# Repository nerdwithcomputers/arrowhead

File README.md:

ARROWHEAD
=========

This is my crack at a cyberdeck that not only I would want to use on the daily as I'm heading to college, but other people would want to use. I decided to go with a traditional clamshell design, which is boring, but only because that might be the only traditional thing on the device (and making sliding mechanisms that last is hard).

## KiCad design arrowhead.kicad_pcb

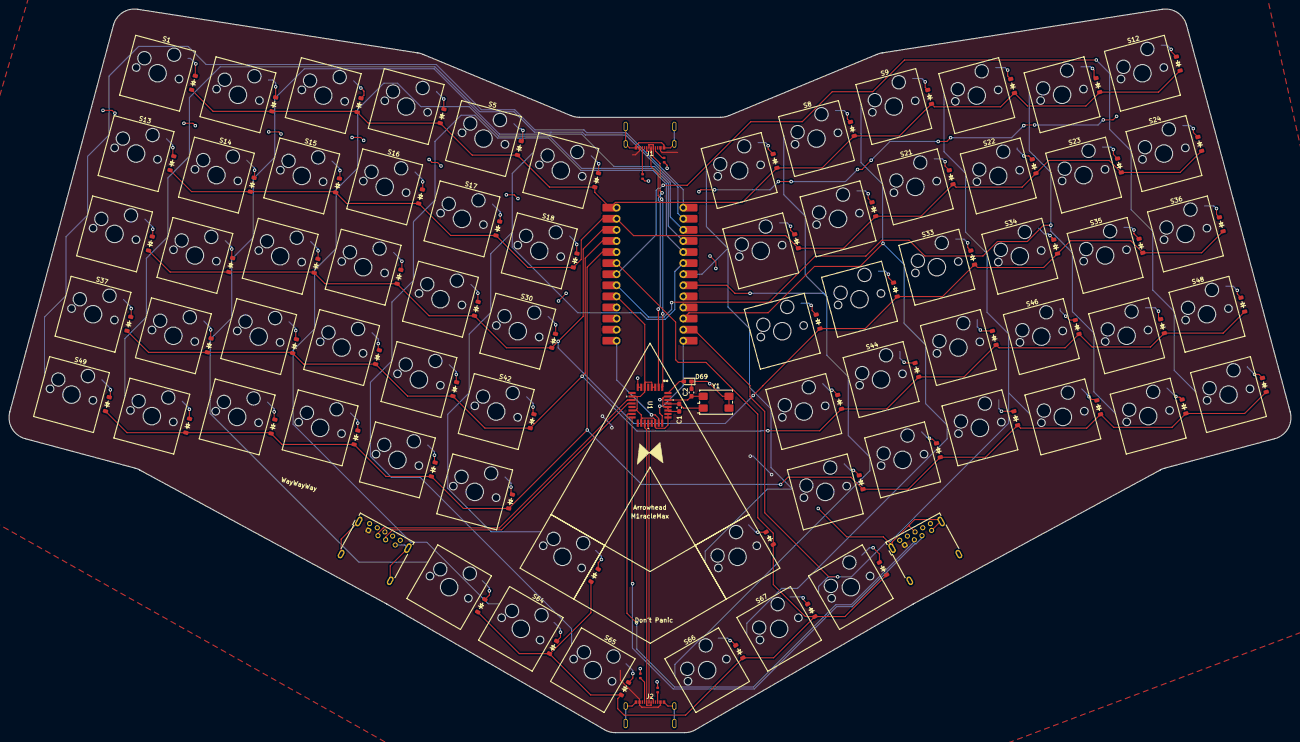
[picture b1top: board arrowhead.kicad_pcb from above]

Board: 2 copper layers, 293.6 x 165.7 mm, 150 parts (0 on the bottom side), 106 nets.

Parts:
C1, C2: C_US; C_0603_1608Metric_Pad1.08x0.95mm_HandSolder
D1, D2, D3, D4, D5, D6, D7, D8, D9, D10, D11, D12, D13, D14, D15, D16, D17, D18, D19, D20, D21, D22, D23, D24, D25, D26, D27, D28, D29, D30, D31, D32, D33, D34, D35, D36, D37, D38, D39, D40, D41, D42, D43, D44, D45, D46, D47, D48, D49, D50, D51, D52, D53, D54, D55, D56, D57, D58, D59, D60, D61, D62, D63, D64, D65, D66, D67, D68: Diode_SOD-123
D69: LED; LED_0603_1608Metric_Pad1.05x0.95mm_HandSolder
J1, J2: USB_C_Receptacle_USB2.0_14P; USB_C_918-418K2024S40000
J3, J4: USB3_A; USB3_A_Molex_48393-001
R1, R2, R3, R4: Resistor; Resistor_0402
S1, S2, S3, S4, S5, S6, S7, S8, S9, S10, S11, S12, S13, S14, S15, S16, S17, S18, S19, S20, S21, S22, S23, S24, S25, S26, S27, S28, S29, S30, S31, S32, S33, S34, S35, S36, S37, S38, S39, S40, S41, S42, S43, S44, S45, S46, S47, S48, S49, S50, S51, S52, S53, S54, S55, S56, S57, S58, S59, S60, S61, S62, S63, S64, S65, S66, S67, S68: Hotswap_MX
U1: TUSB2046BVF; VF32
U2: Adafruit_KB2040_SMD
Y1: Crystal_GND23; Crystal_SMD_7050-4Pin_7.0x5.0mm

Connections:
COL0: S1.1, S13.1, S25.1, S37.1, S49.1, U2.13 (9/PB5)
COL1: S2.1, S14.1, S26.1, S38.1, S50.1, U2.12 (8/PB4)
COL2: S3.1, S15.1, S27.1, S39.1, S51.1, S63.1, U2.11 (7/PE6)
COL3: S4.1, S16.1, S28.1, S40.1, S52.1, S64.1, U2.10 (6/PD7)
COL4: S5.1, S17.1, S29.1, S41.1, S53.1, S65.1, U2.9 (5/PC6)
COL5: S6.1, S18.1, S30.1, S42.1, S54.1, S61.1, U2.8 (4/PD4)
COL6: S7.1, S19.1, S31.1, S43.1, S55.1, S62.1, U2.7 (3/PD0)
COL7: S8.1, S20.1, S32.1, S44.1, S56.1, S66.1, U2.6 (2/PD1)
COL8: S9.1, S21.1, S33.1, S45.1, S57.1, S67.1, U2.3 (RX1/PD2)
COL9: S10.1, S22.1, S34.1, S46.1, S58.1, S68.1, U2.2 (TX0/PD3)
COL10: S11.1, S23.1, S35.1, S47.1, S59.1, U2.19 (A3/PF4)
COL11: S12.1, S24.1, S36.1, S48.1, S60.1, U2.20 (A2/PF5)
GND: C1.2, C2.2, D69.1 (K), J1.A1 (GND), J1.S1 (SHIELD), J2.A1 (GND), J2.S1 (SHIELD), J3.4 (GND), J3.7 (DRAIN), J3.10 (SHIELD), J4.4 (GND), J4.7 (DRAIN), J4.10 (SHIELD), R1.1, R2.1, R3.1, R4.1, U1.7 (GND), U1.8 (BUSPWR), U1.27 (TSTPLL/48MCLK), U1.28 (GND), U1.31 (TSTMODE), U2.4 (GND), U2.5 (GND), U2.16 (GND), Y1.2 (G), Y1.3 (G)
unnamed: D1.2 (A), S1.2
unnamed: D2.2 (A), S2.2
unnamed: D3.2 (A), S3.2
unnamed: D4.2 (A), S4.2
unnamed: D5.2 (A), S5.2
unnamed: D6.2 (A), S6.2
unnamed: D7.2 (A), S7.2
unnamed: D8.2 (A), S8.2
unnamed: D9.2 (A), S9.2
unnamed: D10.2 (A), S10.2
unnamed: D11.2 (A), S11.2
unnamed: D12.2 (A), S12.2
unnamed: D13.2 (A), S13.2
unnamed: D14.2 (A), S14.2
unnamed: D15.2 (A), S15.2
unnamed: D16.2 (A), S16.2
unnamed: D17.2 (A), S17.2
unnamed: D18.2 (A), S18.2
unnamed: D19.2 (A), S19.2
unnamed: D20.2 (A), S20.2
unnamed: D21.2 (A), S21.2
unnamed: D22.2 (A), S22.2
unnamed: D23.2 (A), S23.2
unnamed: D24.2 (A), S24.2
unnamed: D25.2 (A), S25.2
unnamed: D26.2 (A), S26.2
unnamed: D27.2 (A), S27.2
unnamed: D28.2 (A), S28.2
unnamed: D29.2 (A), S29.2
unnamed: D30.2 (A), S30.2
unnamed: D31.2 (A), S31.2
unnamed: D32.2 (A), S32.2
unnamed: D33.2 (A), S33.2
unnamed: D34.2 (A), S34.2
unnamed: D35.2 (A), S35.2
unnamed: D36.2 (A), S36.2
unnamed: D37.2 (A), S37.2
unnamed: D38.2 (A), S38.2
unnamed: D39.2 (A), S39.2
unnamed: D40.2 (A), S40.2
unnamed: D41.2 (A), S41.2
unnamed: D42.2 (A), S42.2
unnamed: D43.2 (A), S43.2
unnamed: D44.2 (A), S44.2
unnamed: D45.2 (A), S45.2
unnamed: D46.2 (A), S46.2
unnamed: D47.2 (A), S47.2
unnamed: D48.2 (A), S48.2
unnamed: D49.2 (A), S49.2
unnamed: D50.2 (A), S50.2
unnamed: D51.2 (A), S51.2
unnamed: D52.2 (A), S52.2
unnamed: D53.2 (A), S53.2
unnamed: D54.2 (A), S54.2
unnamed: D55.2 (A), S55.2
unnamed: D56.2 (A), S56.2
unnamed: D57.2 (A), S57.2
unnamed: D58.2 (A), S58.2
unnamed: D59.2 (A), S59.2
unnamed: D60.2 (A), S60.2
unnamed: D61.2 (A), S61.2
unnamed: D62.2 (A), S62.2
unnamed: D63.2 (A), S63.2
unnamed: D64.2 (A), S64.2
unnamed: D65.2 (A), S65.2
unnamed: D66.2 (A), S66.2
unnamed: D67.2 (A), S67.2
unnamed: D68.2 (A), S68.2
unnamed: D69.2 (A), U1.32 (SUSPND)
unnamed: J1.A5 (CC1), R1.2
unnamed: J1.B5 (CC2), R3.2
unnamed: J2.A5 (CC1), R4.2
unnamed: J2.B5 (CC2), R2.2
unnamed: J3.3 (D+), U1.12 (DP1)
unnamed: J3.2 (D-), U1.11 (DM1)
unnamed: J4.3 (D+), U1.16 (DP2)
unnamed: J4.2 (D-), U1.15 (DM2)
unnamed: J1.A7 (D-), J1.B7 (D-), U1.2 (DM0)
unnamed: J2.A7 (D-), J2.B7 (D-), U1.19 (DM3)
unnamed: U1.23 (DM4), U2.14 (D-)
unnamed: J1.A6 (D+), J1.B6 (D+), U1.1 (DP0)
unnamed: J2.A6 (D+), J2.B6 (D+), U1.20 (DP3)
unnamed: U1.24 (DP4), U2.1 (D+)
unnamed: C2.1, U1.30 (XTAL1), Y1.4
unnamed: C1.1, U1.29 (XTAL2), Y1.1
ROW0: D1.1 (K), D2.1 (K), D3.1 (K), D4.1 (K), D5.1 (K), D6.1 (K), D7.1 (K), D8.1 (K), D9.1 (K), D10.1 (K), D11.1 (K), D12.1 (K), U2.26 (10/PB6)
ROW1: D13.1 (K), D14.1 (K), D15.1 (K), D16.1 (K), D17.1 (K), D18.1 (K), D19.1 (K), D20.1 (K), D21.1 (K), D22.1 (K), D23.1 (K), D24.1 (K), U2.25 (16/PB2)
ROW2: D25.1 (K), D26.1 (K), D27.1 (K), D28.1 (K), D29.1 (K), D30.1 (K), D31.1 (K), D32.1 (K), D33.1 (K), D34.1 (K), D35.1 (K), D36.1 (K), U2.24 (14/PB3)
ROW3: D37.1 (K), D38.1 (K), D39.1 (K), D40.1 (K), D41.1 (K), D42.1 (K), D43.1 (K), D44.1 (K), D45.1 (K), D46.1 (K), D47.1 (K), D48.1 (K), U2.23 (15/PB1)
ROW4: D49.1 (K), D50.1 (K), D51.1 (K), D52.1 (K), D53.1 (K), D54.1 (K), D55.1 (K), D56.1 (K), D57.1 (K), D58.1 (K), D59.1 (K), D60.1 (K), U2.22 (A0/PF7)
ROW5: D61.1 (K), D62.1 (K), D63.1 (K), D64.1 (K), D65.1 (K), D66.1 (K), D67.1 (K), D68.1 (K), U2.21 (A1/PF6)
VCC: U1.3 (VCC), U1.4 (*RESET), U1.6 (EEDATA/GANGED), U1.10 (*OVRCUR1), U1.14 (*OVRCUR2), U1.18 (*OVRCUR3), U1.22 (*OVRCUR4), U1.25 (VCC), U1.26 (*EXTMEM), U2.18 (VCC)
vbus: J1.A4 (VBUS), J2.A4 (VBUS), J3.1 (VBUS), J4.1 (VBUS), U2.15 (RAW)

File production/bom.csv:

Designator,Footprint,Quantity,Value,LCSC Part #
"C1, C2",0201,2,C_US,
"D1, D10, D11, D12, D13, D14, D15, D16, D17, D18, D19, D2, D20, D21, D22, D23, D24, D25, D26, D27, D28, D29, D3, D30, D31, D32, D33, D34, D35, D36, D37, D38, D39, D4, D40, D41, D42, D43, D44, D45, D46, D47, D48, D49, D5, D50, D51, D52, D53, D54, D55, D56, D57, D58, D59, D6, D60, D61, D62, D63, D64, D65, D66, D67, D68, D7, D8, D9",Diode_SOD-123,68,~,
D69,0201,1,LED,
"J1, J2",USB_C_918-418K2024S40000,2,USB_C_Receptacle_USB2.0_14P,
"J3, J4",USB3_A_Molex_48393-001,2,USB3_A,
"R1, R2, R3, R4",Resistor_0402,4,Resistor,
"S1, S10, S11, S12, S13, S14, S15, S16, S17, S18, S19, S2, S20, S21, S22, S23, S24, S25, S26, S27, S28, S29, S3, S30, S31, S32, S33, S34, S35, S36, S37, S38, S39, S4, S40, S41, S42, S43, S44, S45, S46, S47, S48, S49, S5, S50, S51, S52, S53, S54, S55, S56, S57, S58, S59, S6, S60, S61, S62, S63, S64, S65, S66, S67, S68, S7, S8, S9",Hotswap_MX,68,~,
U1,VF32,1,TUSB2046BVF,
U2,Adafruit_KB2040_SMD,1,~,
Y1,Crystal_SMD_7050-4Pin_7.0x5.0mm,1,Crystal_GND23,

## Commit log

2026-05-25 ergogen
2026-05-25 initial readme
2026-05-30 realised the ch334 models aren't available from dk, so I had to redesign
2026-06-08 production run 1
2026-06-14 actual first production run
